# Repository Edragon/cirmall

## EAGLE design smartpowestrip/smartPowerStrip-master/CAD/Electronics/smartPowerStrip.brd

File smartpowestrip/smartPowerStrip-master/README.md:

# Smart Power Strip
----
The ESP8266 has long been a preferred tool for IoT project due to it's cheap price and growing support. This project contains two ways to create an internet connected power strip that interfaces with an Amazon Alexa/echo device. 

Before diving into code, make sure you have installed the necessary libraries:
- Arduino ESP8266 board managers: *File > Preferences > Additional Board Manager URLs:* ``` http://arduino.esp8266.com/stable/package_esp8266com_index.json ```
- Install ESP8266 Libraries: *Sketch > Include Libraries > Manage Libraries... > ESP8266*

----
### Smart Home *(Easy)*

This method emulates multiple WeMo devices on the ESP8266 using the FauxMo library.

Pros:
- Easy to set up. Edit Wifi credentials, update device names, and flash onto esp board.
- Simple utterance for device control: 'Alexa, turn the {device name} on/off'

Cons:
- Limited control. Can only toggle on/off.
- Limited response. Alexa always responds with 'ok'.
- Possible loss of support with device updates
- Only supported by devices with control over UDP (google home does not work)

##### Instructions:
- Open *smartPowerStrip\code\Smart Home\multiFauxMo.ino* and edit the relevant parameters; ssid, password, pin numbers.
- Select the correct board on the arduino IDE and flash. You're now ready to rock. You can rename the switches in your Alexa app.

---- 
### Alexa Skills Kit + Lambda Function + DynamoDB *(Intermediate)*

With this method, the ESP device polls DynamoDB for values, parses the data, and handles the necessary hardware peripherals. The code is also able to update a value (or write a whole new entry) to handle cases where the user wants to update a value via hardware. Using this method gives us the ability to pass more than binary states to our ESP device, opening the door to all kinds of applications. This method was used in the development of the smart power strip project.

Pros:
- Unlimited control and customization. Can read multiple values and datatypes from DynamoDB.
- No need for middle-ware like a MQTT broker. ESP device communicates directly with the cloud.
- Can have custom, elaborate responses from Alexa. 

Cons:
- More difficult setup. Needs to create DynamoDB, install ArduinoAWS libraries, and setup Lambda Function.
- Longer utterance: 'Alexa, tell {skill name} to {intent}'

Common issues:
- Values in DynamoDB are not Strings. Check that the value's are not Number format.

----
### Dimmable, Internet Controlled Power Strip *(Intermediate/Advanced)*
WARNING: If you're not comfortable handling 120VAC don't try this build. Certain loads connected to the power strip could potentially be permanently damaged when dimmed, the system was tested with incandescent bulbs and heaters. 

##### Hardware:
The enclosure was designed with shelving capability to separate the high voltage components from the low voltage ones. The power line was placed on the bottom corner of the face to allow for [strain relief](https://www.sealconusa.com/products/liquid-tight-strain-relief-fittings/nylon/standard/npt/cd13na-bk/) to be installed and a slot was added to allow for re-programming of the ESP chip. After printing, an acrylic sheet was cut with a notch on the side to be used as a shelf support and allow wires to be run between levels. The electronics were assembled, the [receptacles](https://www.digikey.com/product-detail/en/qualtek/738W-X2-03/Q227-ND/245568) were inserted into the appropriate slots, and then soldered to the power leads coming from the dimming module. The cover was then attached to the housing using six M4 screws.

|                  |                    |
|:--------------------------------------------:|:-----------------------------------------------|
|                  |                |

##### Electronics:
To perform AC dimming with a MCU we need a circuit that can handle switching AC voltages and another circuit to tell the controller when the AC wave has crossed zero. For details on the theory view the [Useful Links](#useful-links) section.
The circuit designed detects when the AC wave crosses the zero point and sends a signal to the ESP device (while under optical isolation). The ESP device then counts how many milliseconds have elapsed and toggles a GPIO at the appropiate time. The GPIO outputs to an MOC3020M which opticaslly isolates the MCU device from the high voltage. This signal closes the gate of the TRIAC and let's voltage flow through, turning on the device. A PCB schematic was created, layed out, and sent for manufacture to minimize the footprint of the electronics.

|  |      |
|:--------------------------------------------:|:-----------------------------------------------|
|               |                 |

The PCB was assembled and connected to an [ESP8266 Thing Dev](https://www.sparkfun.com/products/13711) and an [AC-DC Converter](http://a.co/2ixc1vt) from an old iPhone charger. The AC-DC converter connects to a standard 120VAC cable and powers the ESP device which in turn, powers the dimming module. The LEDs serve as a visual indicator that the GPIO is on.

|  | |
|:------------------------------------------------:|:----------------------------------------------------|

##### Embedded Code
The main hurdle with coding this program is the real time control part. The ESP8266 is not designed for real time control so we have to do some acrobatics to get it to perform dimming. The internal clock for the ESP runs at 80Mhz (by default) and we can piggy back off this clock to run the dimmer interrupt. Because this interrupt will run every few microseconds it has to be fast. For this reason, we must add the *ICACHE_RAM_ATTR* directive to our interrupt function to place it in RAM instead of FLASH; not a very well documented directive. The accuracy  of this interrupt seemms  to be +-3us, a negligible error for this application. Below is a diagram of how the code is structured.

##### DynamoDB:
- Create a DynamoDB table with a Partition name as a String and a Sort key as a Number then create a new item for the table. To follow this repo use *devName (String): ESP8266*, *devID (Number): 1*, *onStatus (String): 1*, and *brightLvl (String): 100*.

|     |     |
|:-----------------------------------------------:|:----------------------------------------------|

- Navigate to *AWS site > IAM* and create a user with full access to DynamoDB. This will be used to give the Lambda Function the ESP device read and write priviliges. Now we can work on the embedded code
- Download ArduinoAWS Libraries and copy them to arduino installation directory. In a windows machine *C:\Program Files (x86)\Arduino\libraries*. For more details, go [here](https://github.com/daniele-salvagni/aws-sdk-esp8266)
- Open the *smartPowerStrip\code\AlexaSkillsKit\Embedded Code\Esp8266DynamoDB* directory and copy the keys corresponding the the user created on IAM.
- Edit the code where relevant; AWS_REGION, TABLE_NAME, pSSID, etc. and flash your device. If you're interested to know how the code works, you can go to the [Embedded Code](#embedded-code) section.
- The ESP device should now be able to fetch and push to the cloud! Let's add Alexa to the mix 

##### Lambda Function:
- The Lambda Function will be the middleman between the DynamoDB and the Amazon Echo device. Navigate to *AWS site > Lambda > Functions > Create function*. Assign it the previously created IAM role

- Open up *AlexaSkillsKit\LambdaFunc\index.js* and edit any relevant parameters; *tableName*, *partitionKey*, etc. Once that is done, copy *index.js* and *AlexaSkill.js* into the Function code section. 
- Configure the test event by copying *testEvent.js* into the test event section of the Lambda Function. By default, the test event simulates an Amazon Echo device being told to turn a lamp to 50% brightness.
- From the drop down menu, select the test event created, save your code and hit the test button. The database will update with the value in the test event. You can check the Execution Result for more details.

##### Alexa Skills Kit:
- Now we can add an *Alexa Skills Kit* as a trigger for the Lambda Function. The Disable Skill ID checkbox can be left  unchecked.
- On the Amazon Developer website, create an *Alexa Skills Kit* skill. I suggest making the invocation name something easy to remember like, 'The House'.
- Configure the Interaction Model based on the files in *smartPowerStrip\code\AlexaSkillsKit\speechAssets*. Remember to also add in the Custom Slot Types at the bottom of *IntentSchema.json* and the Sample Utterances provided in the text file.
- On the Configuration tab, select AWS Lambda ARN as the endpoint and paste your Lambda function's ARN. This will tie your custom skill to the Lambda Function created.

- Test the function by entering an utterance in the Service Simulator, 'dim the lamp to 50 percent'. DynamoDB will update and the ESP device will fetch the latest information. Now you have made your own dimming power strip!

##### Demo: 
<br>
The video in the link shows a demonstration of the project. Unforutantely, 'The House' is not an guideline friendly name so it has since been updated to 'Jarvis'. It works nicely for a demo though.

----
### Useful Links:
* [Emulate WeMo device with ESP8266](http://tinkerman.cat/emulate-wemo-device-esp8266/)
* [Microsecond delay on ESP](http://onetechpulse.com/viewtopic.php?t=2)
* [AC dimming tutorial](https://dxarts.washington.edu/wiki/ac-dimmer-circuit)
* [Designing for voice](https://developer.amazon.com/designing-for-voice/)

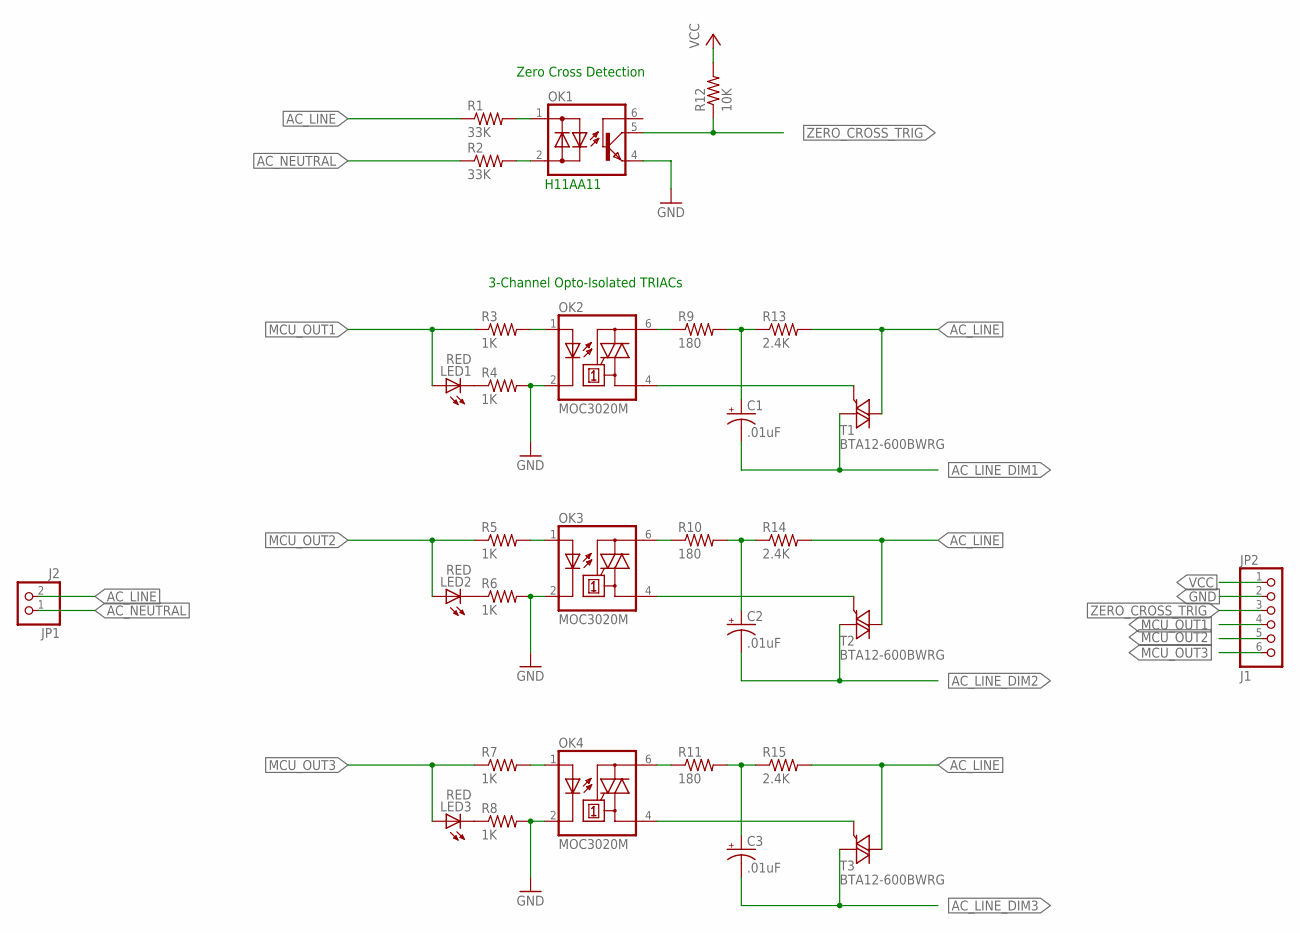
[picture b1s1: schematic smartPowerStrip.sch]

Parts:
C1, C2, C3: .01uF; TT2D5
JP1: J2; 1X02
JP2: J1; 1X06
LED1, LED2, LED3: RED; SFH480
OK1: IL250; DIL06
OK2, OK3, OK4: MOC3020M; DIL06
R1, R2: 33K; 0207/10
R3, R4, R5, R6, R7, R8: 1K; 0309V
R9, R10, R11: 180; 0309V
R12: 10K; 0207/10
R13, R14, R15: 2.4K; 0309V
T1, T2, T3: BTA12-600BWRG; TO220BV

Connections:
AC_LINE: JP1.2, R1.1, R13.2, R14.2, R15.2, T1.T2 (A2), T2.T2 (A2), T3.T2 (A2)
AC_LINE_DIM1: C1.-, T1.T1 (A1)
AC_LINE_DIM2: C2.-, T2.T1 (A1)
AC_LINE_DIM3: C3.-, T3.T1 (A1)
AC_NEUTRAL: JP1.1, R2.1
AC_OUT1: C1.+, R9.2, R13.1
AC_OUT2: C2.+, R10.2, R14.1
AC_OUT3: C3.+, R11.2, R15.1
GND: JP2.2, OK1.4 (E), OK2.2 (C), OK3.2 (C), OK4.2 (C), R4.2, R6.2, R8.2
MCU_OUT1: JP2.4, LED1.A, R3.1
MCU_OUT2: JP2.5, LED2.A, R5.1
MCU_OUT3: JP2.6, LED3.A, R7.1
unnamed: OK3.6 (A2), R10.1
unnamed: OK2.6 (A2), R9.1
unnamed: OK1.2 (AC2), R2.2
unnamed: OK1.1 (AC1), R1.2
unnamed: OK3.1 (A), R5.2
unnamed: OK2.1 (A), R3.2
unnamed: OK2.4 (A1), T1.G
unnamed: OK3.4 (A1), T2.G
unnamed: LED2.K (C), R6.1
unnamed: OK4.6 (A2), R11.1
unnamed: OK4.1 (A), R7.2
unnamed: LED1.K (C), R4.1
unnamed: OK4.4 (A1), T3.G
unnamed: LED3.K (C), R8.1
VCC: JP2.1, R12.2
ZERO_CROSS_TRIG: JP2.3, OK1.5 (C), R12.1

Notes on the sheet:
Zero Cross Detection
3-Channel Opto-Isolated TRIACs
H11AA11

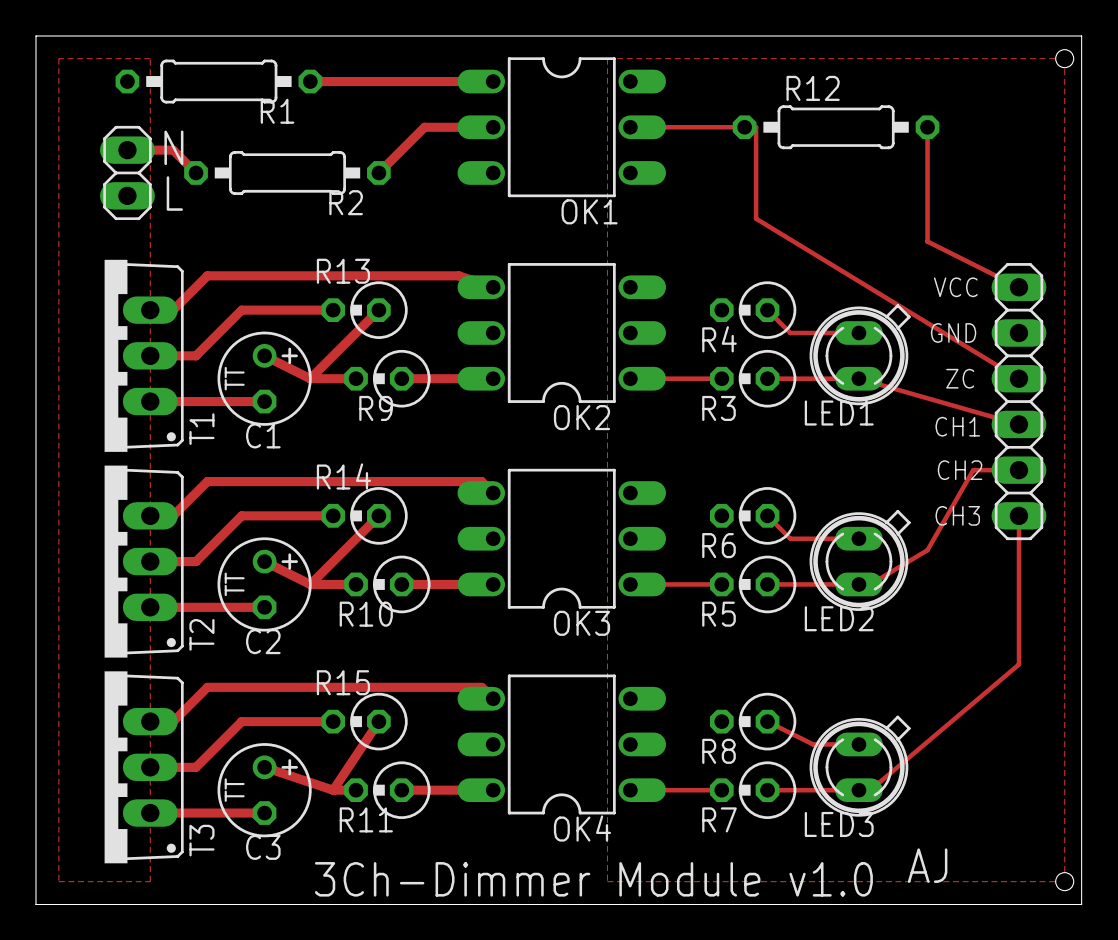
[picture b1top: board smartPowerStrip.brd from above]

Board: 2 copper layers, 58.1 x 48.2 mm, 30 parts (0 on the bottom side), 28 nets.

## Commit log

2018-08-27 init
2018-08-27 humdifier
2018-11-17 1118
2018-11-18 KT1025
2018-11-19 nrf24l01
2018-11-29 1130
2018-12-10 delete
2018-12-17 jlink
2019-08-20 check
